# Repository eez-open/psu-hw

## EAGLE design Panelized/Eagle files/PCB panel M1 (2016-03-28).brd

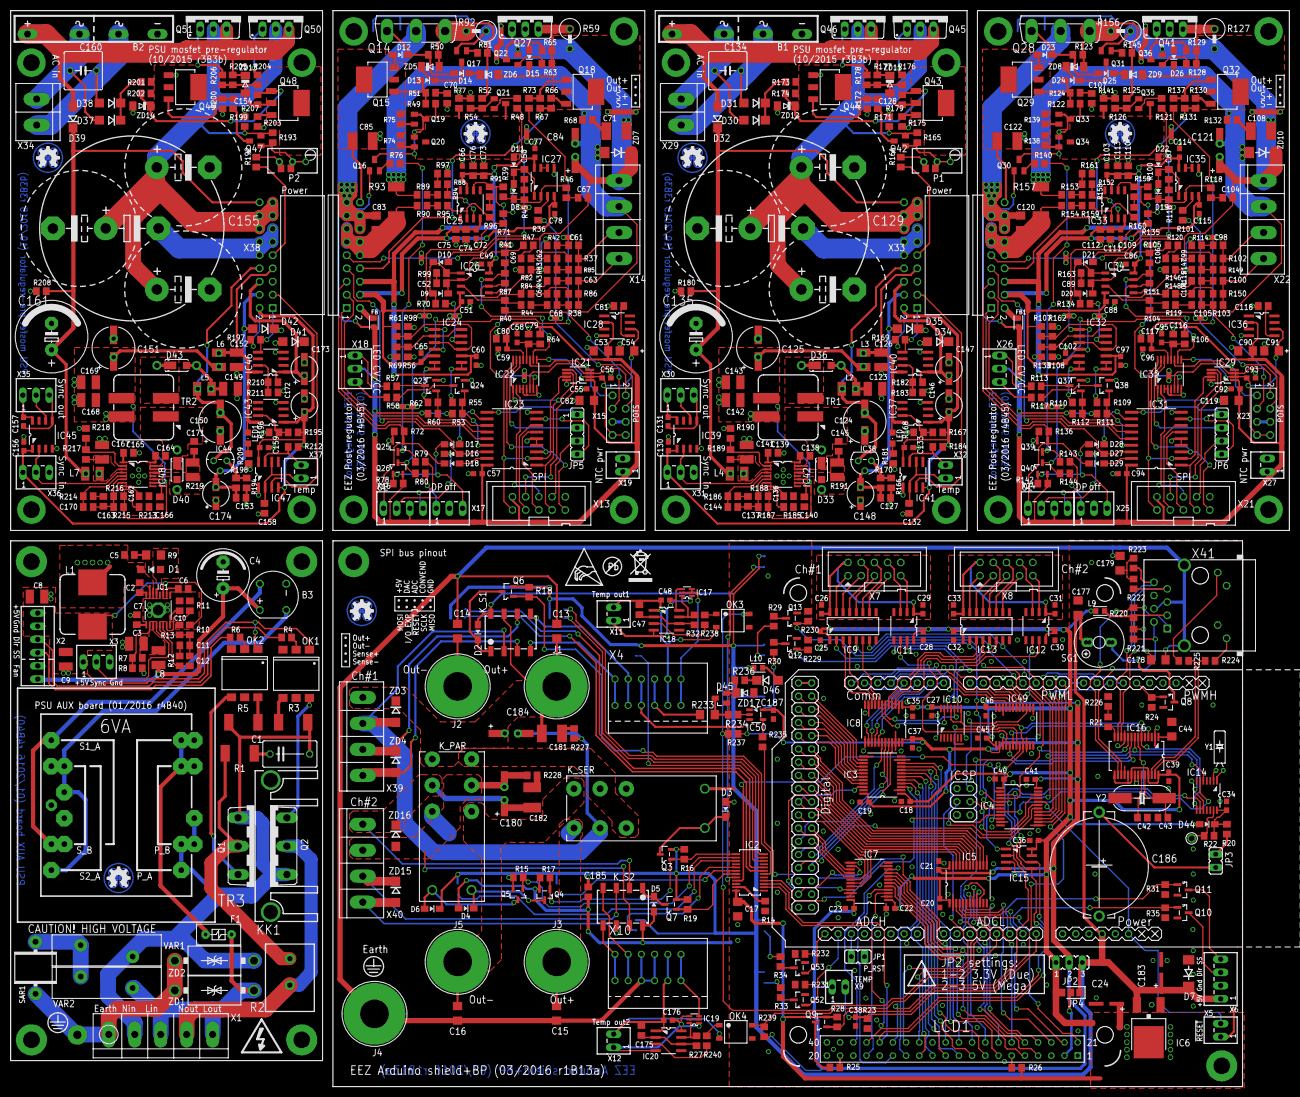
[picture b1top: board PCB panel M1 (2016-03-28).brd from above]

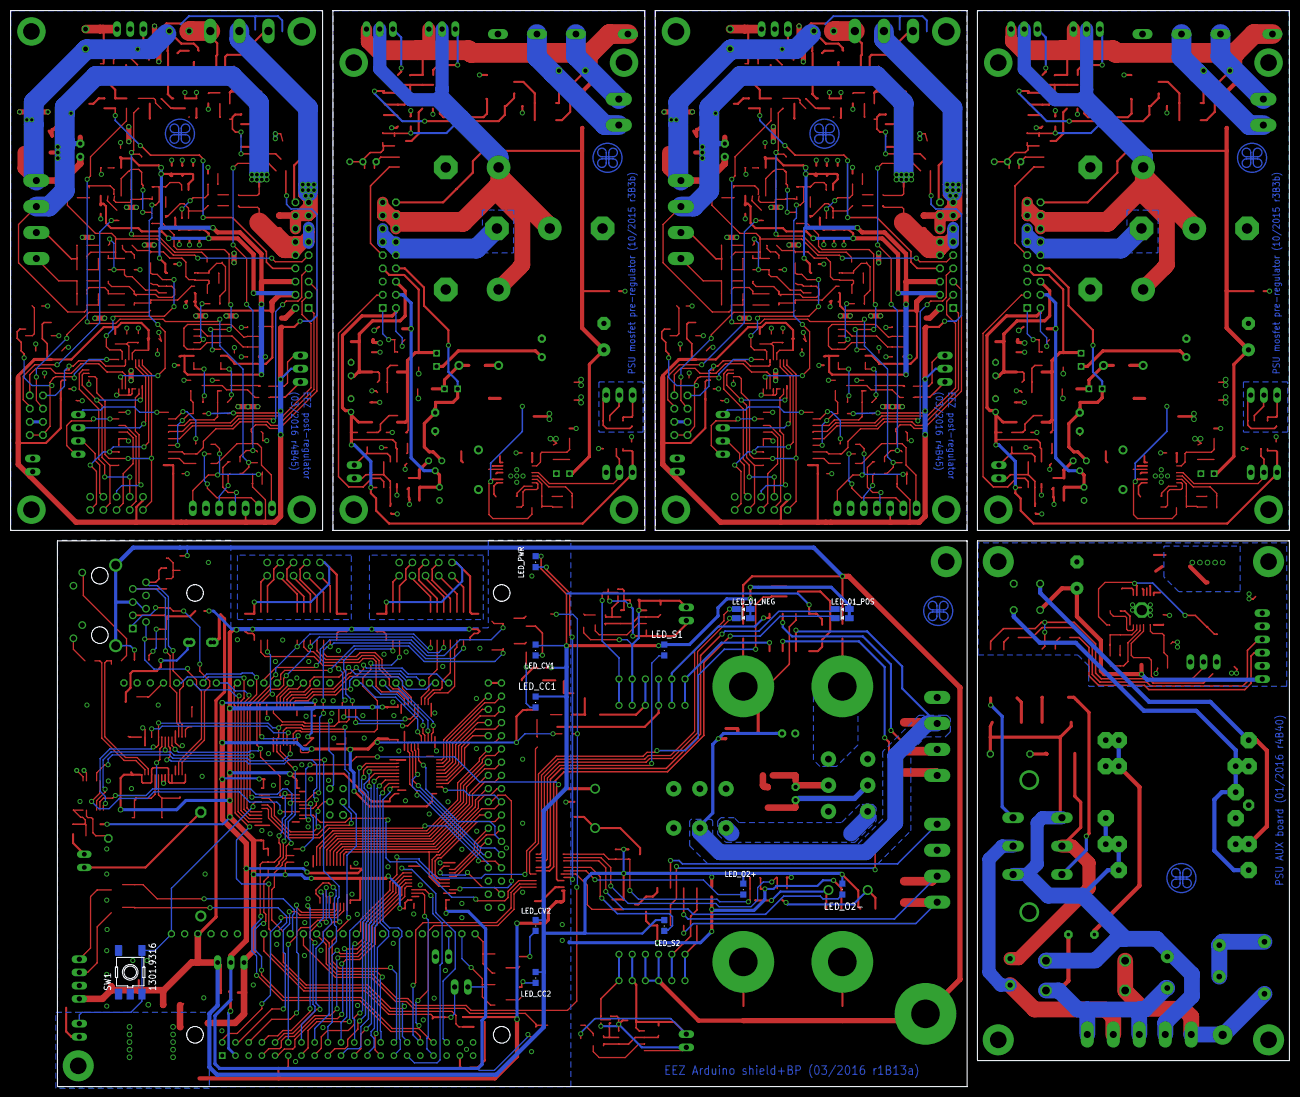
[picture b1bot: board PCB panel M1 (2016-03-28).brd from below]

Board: 3 copper layers, 246.0 x 207.0 mm, 711 parts (12 on the bottom side), 575 nets.

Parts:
B1, B2: GBI20D; GBI20
B3: B40R-DIO; RB1A
C1: 47n/400V; C075-052X106
C2, C6, C132, C138, C158, C164: 22n; C0805
C3, C8, C9: 4u7; C1210
C4: 1mF/25V; ECAP5/10.5
C5, C145, C171: 330p; C0805
C7, C127, C139, C153, C165: 100n; C0805
C10: 820p; C0805
C11: 3n9; C0805
C12: 180p; C0805
C13, C14, C15, C16, C178, C179: 10n; C1206
C17, C44, C53, C82, C90, C119, C177: 10u; C1206
C18, C19, C20, C21, C22, C23, C25, C26, C27, C28, C29, C30, C31, C32, C33, C34, C35, C36, C37, C38, C39, C40, C41, C45, C46, C48, C49, C51, C55, C56, C57, C58, C59, C60, C65, C66, C72, C77, C78, C86, C88, C92, C93, C94, C95, C96, C97, C102, C103, C109, C114, C115, C130, C131, C133, C156, C157, C159, C176, C187: 100n; C0603
C24: 10u; PANASONIC_C
C42, C43: 18p; C0805
C47, C175: 47n; C0805
C50, C67, C87, C104: 1n; C0805
C52, C89: 120p; C0805
C54, C91: 10u (Tant.); EC1206
C61, C63, C98, C100: 47p; C0805
C62, C64, C99, C101: 2n2; C0805
C68, C69, C105, C106: 1n5; C0805
C70, C74, C76, C107, C111, C113: 10n; C0805
C71, C85, C108, C122: 470n; C1812
C73, C75, C79, C80, C81, C110, C112, C116, C117, C118, C185: 1u; C0805
C83, C120: 1u/100V; C1206
C84, C121, C180, C184: 22u/63V; CAPAE660X610N_COMBO2
C123, C126, C142, C143, C149, C152, C168, C169: 2u2; C1210
C124, C125, C150, C151: 47u; CAPAE660X610N_COMBO
C128, C154: 560p; C0805
C129, C155: 10000u; ED35D+3XED22.5_COMBO
C134, C160: 1u; C050-075X075
C135, C161: 470u; ECAP5/13
C136, C162: 4n7; C0805
C137, C163: 6n8; C0805
C140, C166: 33n; C0805
C141, C167: 2u2/100V; C1210
C144, C170: n.c.; C0805
C146, C147, C172, C173: EEEFK1V100R; CAPAE430X610N_COMBO
C148, C174: EEEFK1V220R; CAPAE430X610N_COMBO
C181, C182: 470n/100V; C1812
C183: 47u; PANASONIC_C
C186: EECS5R5H105; SG-R20MM
D1: DFLS1100-7; SOD123
D2, D3, D4, D5, D6, D8, D9, D10, D11, D12, D13, D14, D15, D16, D17, D18, D19, D20, D21, D22, D23, D24, D25, D26, D27, D28, D29, D44: BAS316; SOD323-W
D7: SMBJ5.0A-TR; DO214AA
D30, D31, D32, D37, D38, D39: S1G; DO214AC
D33, D36, D40, D43: SR1100; DO34+SOD123
D34, D35, D41, D42, D46: SKL16; DO214AC
D45: BAT54S; SOT23
EEZ_SIGNATURE, EEZ_SIGNATURE1, EEZ_SIGNATURE2, EEZ_SIGNATURE3, EEZ_SIGNATURE4, EEZ_SIGNATURE5: SIGNATURESMALL; SIGNATURE_5MM
F1: LX008-V2 (80mA); POLYSWITCH-R7
FB, FB1: 60R@100MHz; BEAD0603
IC1: LM25575; SOP65P640X110-17N_HOLE
IC2: TLC5925; SOP63P600X175-24N
IC3, IC4, IC5, IC7, IC8, IC49: SN74LVCC3245ADBRSSOP; SOP65P780X200-24N
IC6: LD1117ADT33TR; DPACK
IC9, IC13: Si8660EC-B-IS1; SOIC-16
IC10: SN74LV125APW; SOP65P640X120-14N
IC11, IC12: SI8620EC-B-IS; SOIC127P600X173-8N
IC14: PCA21125; SOP65P640X120-14N
IC15: AT25256B; SOIC127P600X175-8N
IC16: ENC28J60-I/SS; SOP65P780X200-28N
IC17, IC19: BC857BS; SOT65P210X110-6N
IC18, IC20: NE555D; SOIC127P600X175-8N
IC21, IC29: DAC8552; DGK8-M
IC22, IC30: ADS1120; PW(R-PDSO-G16)
IC23, IC31: MCP23S08-E/SO; SOIC127P1030X265-18N
IC24, IC32: LP339D; SO14
IC25, IC33: OP27GSZ; SOIC127P600X173-8N
IC26, IC27, IC34, IC35: TL072D; SOIC127P600X173-8N
IC28, IC36: REF5025; SOIC127P600X175-8N
IC37, IC40, IC43, IC46: LP2951SO8; SOIC127P600X175-8N
IC38, IC44: LM337LZ; TO92
IC39, IC45: Si8610BC-B-IS; SOIC127P600X173-8N
IC41, IC47: TLC555; SOIC127P600X175-8N
IC42, IC48: LM5574; SOP65P640X110-16N
IC50: SN74LV1T34; SOT95P280X145-5N
J1, J3: BS-244DSM-R; BP_5_12
J2, J5: BS-244DSM-B; BP_5_12
J4: BS-244DSM-G; BP_5_12
JP1, JP3: 826926-2; JP1
JP2: 826926-3; JUMPER_3-PIN
JP4: 0R-JUMPA; A0R-JMP
JP5, JP6: JP4
KK1: SK145/37,5; SK145
K_PAR: RT424005; RT-C/016A5_ROUND
K_S1, K_S2: G6K-2F-5DC; G6K-2F
K_SER: RT424005; RT-C/016A5_ROUND
L1: 100uH (MSS1260-104K); MSS1278
L2, L3, L4, L5, L6, L7: 2u2; L1210_COMBO
L8: 2u2; L1210
L9, L10: 60R@100MHz; BEAD0603
LCD1: TFT_320QVT; LCD_TFT_320QVT_MIRROR
LED, LED1: HSMY-C170; CHIPLED_0805
LED_01_NEG, LED_01_POS: HSMF-C155; LED_KPB-3025
LED_CC1, LED_CC2: HSMH-C170; CHIPLED_0805
LED_CV1, LED_CV2: L-934YD; CHIPLED_0805
LED_O2+, LED_O2-: HSMG-C170; CHIPLED_0805
LED_PWR: HSMR-C170; CHIPLED_0805
LED_S1, LED_S2: HSMY-C170; CHIPLED_0805
MCU: ARDUINO+ICSP_MIRROR
OK1: MOC3052; DIL6-SMD
OK2: MOC3062; DIL6-SMD
OK3, OK4: HCPL-181
P1, P2: 500K; R_TRIM+R0805
Q1, Q2: BTA26-600; TOP3S-1
Q3, Q5, Q6, Q7, Q9: IRLML2246TRPBF; SOT95P237X112-3N
Q4, Q8, Q10, Q11, Q12, Q13, Q23, Q24, Q25, Q37, Q38, Q39, Q52, Q53: 2N7002; SOT103P240X110-3N
Q14, Q28: IRFP250N; TO247BV
Q15, Q18, Q29, Q32, Q43, Q48: BCP56-16.115; SOT230P700X180-4N
Q16, Q21, Q30, Q35: MMBT5551; SOT23-BEC
Q17, Q31: BC846C; SOT23-BEC
Q19, Q20, Q33, Q34, Q42, Q47: MMBT5401; SOT23-BEC
Q22, Q36: BC857C; SOT23-BEC
Q26, Q40: BSS84P; SOT95P237X112-3N
Q27, Q41: IRF9640; TO220B-VMOS
Q44, Q49: MCR08MT1G; SOT230P700X180-4N
Q45, Q46, Q50, Q51: IRF5210PBF; TO220B-VMOS
R1: 150R/2W; R2512
R2: 15R/7W; R_0913
R3, R5: 330R/2W; R2512
R4, R6: 270R; R0805
R7: 15K; R0805
R8, R36, R39, R50, R56, R63, R65, R100, R101, R108, R123, R128, R129: 2K2; R0805
R9: 10R; R1206
R10: 5K6 1%; R0805
R11, R185, R213: 30K; R0805
R12, R85, R86, R149, R150, R186, R214: 20K; R0805
R13: 1K8 1%; R0805
R14, R27, R32, R177, R190, R205, R218, R237, R239: 1K5; R0805
R15, R17, R24, R28, R31, R35, R72, R78, R136, R142, R229, R230, R231, R232: 100K; R0805
R16, R18, R19, R23, R171, R172, R199, R200: 4K7; R0805
R20, R54, R126, R181, R209: 560R; R0805
R21: 2K2 1%; R0805
R22, R26, R40, R41, R42, R43, R46, R70, R71, R73, R98, R104, R105, R114, R115, R118, R134, R135, R137, R162, R169, R174, R197, R202: 10K; R0805
R25, R64, R106: 10R; R0805
R29, R30, R33, R34, R57, R58, R79, R80, R113, R117, R143, R144: 240R; R0805
R37, R38, R102, R103: 2K; R0805
R44, R47, R66, R74, R75, R119, R120, R130, R138, R139: 220R; R0805
R45, R116: 11K; R0805
R48, R51, R121, R124: 470R; R0805
R49, R122, R175, R176, R178, R203, R204, R206, R236: 100R; R0805
R52, R125: 16K; R0805
R53, R60, R111, R112: 5K1; R0805
R55, R62, R109, R110: 5K6; R0805
R59, R127: 2R2/2W; 0411V
R61, R107: 12K; R0805
R67, R81, R131, R145, R234, R235: 1K; R0805
R68, R132, R227, R228: 1R; R0805
R69, R133: 47K; R0805
R76, R140: 1K8; R0805
R77, R141: 51K; R0805
R82, R87, R146, R151: 7K5; R0805
R83, R84, R147, R148: 130K; R0805
R88, R91, R152, R155, R184, R212: 3K9; R0805
R89, R90, R94, R95, R153, R154, R158, R159: 51R; R0805
R92, R156: 0R1/3W; 0411V
R93, R157: R020/2W; R2512
R96, R97, R160, R161, R238, R240: 180R; R0805
R99, R163: 0R; R0805
R164, R192: 82K; R0805
R165, R189, R193, R217: 39K; R0805
R166, R194: 604R 1%; R0805
R167, R182, R195, R210: 12K 1%; R0805
R168, R183, R196, R211: 3K9 1%; R0805
R170, R198: 200R 1%; R0805
R173, R201: 3K3; R0805
R179, R180, R207, R208: 18K; R0805
R187, R215: 30K 1%; R0805
R188, R216: 4K7 1%; R0805
R191, R219: 10R; R1210
R220, R221, R222, R223: 49R9; R0805
R224, R225: 200R; R0805
R226: 120R 1%; R0805
R233: 10K; R1206
SAR1: CG2-470L; SAR
SG1: LD-BZEN-0903; BUZZER
SH1, SH2: GND; SHORT
SH3, SH4: SHORT_2
SW1: 1301.9316; TACTM-6XN
TP1: PCB_SHIELD_TAB
TR1, TR2: MSD1260-824; MSD1260
TR3: 12V/6VA; PCB_TRAFO6VA_DUAL
U$2: RECYCLE_BIN1/8
U$3: PB_SMALL
U$4: ESD_SYMBOL
VAR1, VAR2: S20K275; VARISTOR
X1: AC_IN; TBLOCK5.0_5
X2: 22-23-2041; 22-23-2061
X3, X17, X18, X25, X26, X30, X31, X35, X36: 22-23-2031
X4, X10: MC000005; MC000005_MIRROR
X5, X9, X11, X12, X19, X27, X32, X37: 22-23-2021
X6, X16, X24: 22-23-2041
X7, X8: 09185106324; IDC-10PIN
X13, X21: 09185106324; PAK100/2500-10
X14, X22, X39, X40: 282836-4; TBLOCK5.0_4
X15, X23: TSW-104-08-L-D; TSW-104-02-S-D
X20, X28: TSW-109-08-L-D-RA
X29, X34: AC In; TBLOCK5.0_2
X33, X38: SSW-109-02-T-D-RA
X41: LMJTAB881243M-L; RJ45-TRAFO-LED
Y1: 32,768kHz; R26_XTAL
Y2: 25MHz; HC-49/4H
ZD1, ZD2: 1.5KE400CA; DO201-BIDIR
ZD3, ZD4, ZD15, ZD16: P4SMAJ60A; DO214AC
ZD5, ZD8, ZD11, ZD13: 13V; MINIMELF
ZD6, ZD9: 6V2; MINIMELF
ZD7, ZD10: P6SMB68A; DO214AA
ZD12, ZD14: 5V6; MINIMELF
ZD17: 4V3; MINIMELF

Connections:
3V3BP_SELECT: IC2.4, IC4.9
3V3LCDSD_CS: IC7.10, LCD1.38
3V3LCD_CS: IC7.4, LCD1.15
3V3LCD_DB0: IC5.3, LCD1.21
3V3LCD_DB1: IC5.4, LCD1.22
3V3LCD_DB2: IC5.5, LCD1.23
3V3LCD_DB3: IC5.6, LCD1.24
3V3LCD_DB4: IC5.7, LCD1.25
3V3LCD_DB5: IC5.8, LCD1.26
3V3LCD_DB6: IC5.9, LCD1.27
3V3LCD_DB7: IC5.10, LCD1.28
3V3LCD_DB8: IC3.10, LCD1.7
3V3LCD_DB9: IC3.9, LCD1.8
3V3LCD_DB10: IC3.8, LCD1.9
3V3LCD_DB11: IC3.7, LCD1.10
3V3LCD_DB12: IC3.6, LCD1.11
3V3LCD_DB13: IC3.5, LCD1.12
3V3LCD_DB14: IC3.4, LCD1.13
3V3LCD_DB15: IC3.3, LCD1.14
3V3LCD_RD: LCD1.6, R26.1
3V3LCD_RESET: IC7.3, LCD1.17
3V3LCD_RS: IC7.6, LCD1.4
3V3LCD_WR: IC7.5, LCD1.5
3V3MISO: IC10.8, IC10.11, IC14.8, IC15.2, IC16.6, IC49.9, LCD1.35
3V3MOSI: IC2.2, IC4.5, IC9.2, IC13.2, IC14.9, IC15.5, IC16.7, LCD1.37
3V3RTC_SELECT: IC4.8, IC14.6
3V3SCLK: IC2.3, IC4.3, IC9.7, IC13.7, IC14.10, IC15.6, IC16.8, LCD1.36
3V3TOUCH_CS: IC7.8, LCD1.30
3V3TOUCH_DIN: IC7.9, LCD1.31
3V3TOUCH_DO: IC49.8, LCD1.33
3V3TOUCH_IRQ: IC49.7, LCD1.34
3V3TOUCH_SCLK: IC7.7, LCD1.29
!3V3ADC1_SELECT: IC8.8, IC9.6
!3V3ADC2_SELECT: IC8.3, IC13.6
!3V3BP_OE: IC2.21, IC4.10
!3V3CONVEND1: IC11.6, IC49.4
!3V3CONVEND2: IC12.6, IC49.3
!3V3DAC1_SELECT: IC8.9, IC9.4
!3V3DAC2_SELECT: IC8.4, IC13.4
!3V3EEPROM_SELECT: IC4.6, IC15.1
!3V3ETH_IRQ: IC16.4, IC49.6
!3V3ETH_SELECT: IC4.7, IC16.9
!3V3IO_EXPANDER1: IC8.10, IC9.3
!3V3IO_EXPANDER2: IC8.5, IC13.3
!3V3ISOLATOR1_EN: IC8.7, IC10.13
!3V3ISOLATOR2_EN: IC8.6, IC10.10
!3V3RESET: IC4.4, IC9.5, IC13.5, IC16.10
!3V3RTC_IRQ: IC14.5, IC49.5
!ADC1_SELECT: IC8.16, MCU.15
!ADC2_SELECT: IC8.21, MCU.48
!BP_OUT1: IC2.6, Q6.1, R18.1
!BP_OUT2: IC2.7, LED_01_POS.4
!BP_OUT3: IC2.8, LED_01_POS.2
!BP_OUT5: IC2.10, LED_S1.C
!BP_OUT6: IC2.11, LED_01_NEG.4
!BP_OUT7: IC2.12, LED_01_NEG.2
!BP_OUT8: IC2.13, Q3.1, Q4.1, R16.1, R17.2
!BP_OUT9: IC2.14, Q5.1, R15.1
!BP_OUT10: IC2.15, LED_O2-.C
!BP_OUT12: IC2.17, LED_S2.C
!BP_OUT13: IC2.18, LED_O2+.C
!BP_OUT14: IC2.19, Q7.1, R19.1
!BP_OUT15: IC2.20, LED_PWR.C
!CC_ACTIVE: IC23.12, Q23.1, R60.1, R62.2
!CC_ACTIVE1: IC31.12, Q37.1, R110.2, R112.1
!CH1_ADC: IC9.11, X7.6
!CH1_DAC: IC9.13, X7.4
!CH1_EXPANDER: IC9.14, X7.3
!CH1_INT: IC11.3, X7.8
!CH1_RESET: IC9.12, X7.5
!CH2_ADC: IC13.11, X8.6
!CH2_DAC: IC13.13, X8.4
!CH2_EXPANDER: IC13.14, X8.3
!CH2_INT: IC12.3, X8.8
!CH2_RESET: IC13.12, X8.5
!CONVEND1: IC49.20, MCU.21
!CONVEND2: IC49.21, MCU.20
!CV_ACTIVE: IC23.15, Q24.1, R53.1, R55.2
!CV_ACTIVE1: IC31.15, Q38.1, R109.2, R111.1
!DAC1_SELECT: IC8.15, MCU.16
!DAC2_SELECT: IC8.20, MCU.47
!DP_DRIVE: Q18.1, R67.1, R73.1
!DP_DRIVE1: Q32.1, R131.1, R137.1
!EEPROM_SELECT: IC4.18, MCU.49
!ETH_IRQ: IC49.18, MCU.18
!ETH_SELECT: IC4.17, MCU.11
!INT: JP5.3, X13.8
!INT1: JP6.3, X21.8
!IO_EXPANDER1: IC8.14, MCU.17
!IO_EXPANDER2: IC8.19, MCU.46
!ISOLATOR1_EN: IC8.17, MCU.14
!ISOLATOR2_EN: IC8.18, MCU.45
!PS_DRDY: IC22.14, JP5.2
!PS_DRDY1: IC30.14, JP6.2
!PS_RESET: IC23.6, X13.5
!PS_RESET1: IC31.6, X21.5
!PWD_RST: JP1.1, MCU.A13
!RESET: IC4.20, MCU.RESET, SW1.3, SW1.4, X5.2
!RTC_IRQ: IC49.19, MCU.19
!SET_100%: IC23.14, X20.7
!SET_100%1: IC31.14, X28.7
!SET_DP: D17.C, IC23.11
!SET_DP1: D28.C, IC31.11
+3V3: C17.1, C18.1, C20.1, C22.1, C24.1, C25.1, C27.2, C28.1, C30.1, C32.1, C35.1, C36.1, C39.1, C40.1, C45.1, D44.A, IC2.24, IC3.1, IC4.1, IC5.1, IC6.4, IC7.1, IC8.1, IC9.1, IC10.14, IC11.8, IC12.8, IC13.1, IC15.3, IC15.7, IC15.8, IC16.15, IC16.19, IC16.20, IC16.25, IC16.28, IC49.1, JP2.1, JP4.3, L9.P$2, Q9.2, R26.2, R28.2
+5V: C177.2, C183.1, C185.1, D6.C, D7.C, IC6.3, JP2.3, JP4.1, L10.P$1, LED_01_NEG.1, LED_01_NEG.3, LED_01_POS.1, LED_01_POS.3, LED_CC1.A, LED_CC2.A, LED_CV1.A, LED_CV2.A, LED_O2+.A, LED_O2-.A, LED_PWR.A, LED_S1.A, LED_S2.A, MCU.5V, Q3.2, Q5.2, Q6.2, Q7.2, R15.2, R16.2, R18.2, R19.2, SG1.+, SG1.+B, X6.1
+5V1: C53.1, C55.2, C57.1, C59.2, C80.2, C82.1, FB.P$2, IC21.1, IC22.13, IC23.18, IC28.2, Q16.B, Q26.2, R53.2, R60.2, R64.1, R78.1, X13.2, X16.3, X18.2, X19.1
+5V2: C90.1, C92.2, C94.1, C96.2, C117.2, C119.1, FB1.P$2, IC29.1, IC30.13, IC31.18, IC36.2, Q30.B, Q40.2, R106.1, R111.2, R112.2, R142.1, X21.2, X24.3, X26.2, X27.1
+5V3: C130.1, C133.1, C146.1, C146.1.1, IC37.1, IC39.1, IC41.4, IC41.8, R167.1, R169.2, R184.2, X31.1, X33.2
+5V4: C156.1, C159.1, C172.1, C172.1.1, IC43.1, IC45.1, IC47.4, IC47.8, R195.1, R197.2, R212.2, X36.1, X38.2
+5V_CH1: C48.1, IC17.1, IC17.4, IC18.4, IC18.8, X11.1
+5V_CH2: C176.1, IC19.1, IC19.4, IC20.4, IC20.8, X12.1
+VNR: C126.1, IC37.8, IC40.8, L3.2, L3.2.1, LED.A, X33.7
+VNR1: C152.1, IC43.8, IC46.8, L6.2, L6.2.1, LED1.A, X38.7
+VREF: C54.+, C56.2, IC21.2, IC22.9, IC28.6, X15.7, X15.8
+VREF1: C91.+, C93.2, IC29.2, IC30.9, IC36.6, X23.7, X23.8
-9V: R66.2, R67.2, X20.8
-9V1: R130.2, R131.2, X28.8
-VNR: C124.2, C124.2.1, IC38.3, L2.2, L2.2.1, X33.8
-VNR1: C150.2, C150.2.1, IC44.3, L5.2, L5.2.1, X38.8
AC_EARTH: SAR1.P$2, X1.1, ZD1.C, ZD2.C
AC_IN1: C1.2, Q1.A1, Q2.A1, R3.2, R5.2, TR3.NC1, TR3.P1, TR3.P1.1, TR3.P1.2, VAR1.P$2, X1.2, ZD2.A
AC_IN2: F1.P$1, VAR2.P$1, X1.3, X1.5, ZD1.A
BATT_NTC1: MCU.A4, OK3.4, R237.2
BATT_NTC2: MCU.A3, OK4.4, R239.2
BP_OE: IC4.14, MCU.10
BP_SELECT: IC4.15, MCU.9
BUZZER: MCU.12, Q8.1, R24.2
CC_LED: R57.2, X18.1
CC_LED1: R113.2, X26.1
CH1_5VDC: C26.1, C29.1, IC9.16, IC11.1, X7.2
CH1_GND: C26.2, C29.2, IC9.9, IC11.4, X7.10
CH1_MISO: IC11.2, X7.9
CH1_MOSI: IC9.15, X7.1
CH1_SCLK: IC9.10, X7.7
CH2_5VDC: C31.1, C33.1, IC12.1, IC13.16, X8.2
CH2_GND: C31.2, C33.2, IC12.4, IC13.9, X8.10
CH2_MISO: IC12.2, X8.9
CH2_MOSI: IC13.15, X8.1
CH2_SCLK: IC13.10, X8.7
CS_ADC: IC22.2, X13.6
CS_ADC1: IC30.2, X21.6
CS_DAC: IC21.5, X13.4
CS_DAC1: IC29.5, X21.4
CS_EXPANDER: IC23.7, X13.3
CS_EXPANDER1: IC31.7, X21.3
CV_LED: R58.1, X18.3
CV_LED1: R117.1, X26.3
DC_IN: C83.1, Q14.D, X20.14, X20.15, X20.16, X20.17
DC_IN1: C120.1, Q28.D, X28.14, X28.15, X28.16, X28.17
DC_IN2: B1.+, D32.A, Q45.S, Q46.S, R177.1, ZD11.C
DC_IN3: B2.+, D39.A, Q50.S, Q51.S, R205.1, ZD13.C
DC_OUT: C135.+, D32.C, L4.1, L4.1.1, R180.1, X33.18
DC_OUT1: C161.+, D39.C, L7.1, L7.1.1, R208.1, X38.18
DC_PREG1: C141.1, IC42.3, L4.2, L4.2.1, R189.2
DC_PREG2: C167.1, IC48.3, L7.2, L7.2.1, R217.2
DC_PREG3: C3.1, IC1.3, L8.2, R7.2
DP_LED: Q26.3, R73.2, R80.2
DP_LED1: Q40.3, R137.2, R144.2
EARTH: C13.2, C14.1, C15.2, C16.1, C178.2, C179.2, J4.P$1, X10.3, X10.3.1, X10.4, X10.4.1, X41.4, X41.5, X41.SH1, X41.SH2
ETH_IN+: IC16.13, R223.1, X41.8
ETH_IN-: IC16.12, R222.2, X41.7
ETH_LEDA: IC16.26, R225.1
ETH_LEDB: IC16.27, R224.1
ETH_OUT+: IC16.17, R221.1, X41.2
ETH_OUT-: IC16.16, R220.2, X41.1
EXT_TRIG: MCU.A7, R235.1
GND: B3.-, C3.2, C4.-, C6.2, C7.1, C8.2, C9.2, C10.1, IC1.9, IC1.12, IC1.TP, IC1.TP2, R8.1, R11.2, R13.2, X2.2, X2.5, X3.3
GND1: C49.1, C51.1, C53.2, C54.-, C55.1, C56.1, C57.2, C58.1, C59.1, C60.1, C65.1, C66.2, C70.2, C72.2, C73.1, C74.1, C75.1, C76.1, C77.1, C78.1, C79.1, C80.1, C81.2, C82.2, C83.2, C85.2, IC21.8, IC22.3, IC22.4, IC22.5, IC22.8, IC23.4, IC23.5, IC23.9, IC27.5, IC28.4, Q23.2, Q24.2, Q25.2, Q27.D, R54.1, R56.1, R72.1, R77.1, R82.1, R97.1, R98.2, SH1.1, X13.10, X15.5, X15.6, X17.2, X19.2, X20.12
GND2: C86.1, C88.1, C90.2, C91.-, C92.1, C93.1, C94.2, C95.1, C96.1, C97.1, C102.1, C103.2, C107.2, C109.2, C110.1, C111.1, C112.1, C113.1, C114.1, C115.1, C116.1, C117.1, C118.2, C119.2, C120.2, C122.2, IC29.8, IC30.3, IC30.4, IC30.5, IC30.8, IC31.4, IC31.5, IC31.9, IC35.5, IC36.4, Q37.2, Q38.2, Q39.2, Q41.D, R108.1, R126.1, R136.1, R141.1, R146.1, R161.1, R162.2, SH2.1, X21.10, X23.5, X23.6, X25.2, X27.2, X28.12
GND4: B1.-, C123.2, C124.1, C124.1.1, C125.2, C125.2.1, C126.2, C127.1, C129.-, C129.-1, C129.-2, C129.-3, C130.2, C132.1, C133.2, C135.-, C136.1, C139.1, C140.2, C141.2, C142.2, C143.2, C146.2, C146.2.1, C147.2, C147.2.1, C148.1, C148.1.1, D34.A, D35.C, IC37.4, IC39.4, IC40.4, IC41.1, IC42.9, IC42.12, Q44.1, R166.2, R168.2, R172.2, R175.2, R179.2, R180.2, R181.2, R183.2, R185.2, R188.2, R190.1, SH3.2, TR1.4, X31.3, ZD12.A
GND6: B2.-, C149.2, C150.1, C150.1.1, C151.2, C151.2.1, C152.2, C153.1, C155.-, C155.-1, C155.-2, C155.-3, C156.2, C158.1, C159.2, C161.-, C162.1, C165.1, C166.2, C167.2, C168.2, C169.2, C172.2, C172.2.1, C173.2, C173.2.1, C174.1, C174.1.1, D41.A, D42.C, IC43.4, IC45.4, IC46.4, IC47.1, IC48.9, IC48.12, Q49.1, R194.2, R196.2, R200.2, R203.2, R207.2, R208.2, R209.2, R211.2, R213.2, R216.2, R218.1, SH4.2, TR2.4, X36.3, ZD14.A
GND7: C17.2, C18.2, C19.1, C20.2, C21.1, C22.2, C23.1, C24.2, C25.2, C27.1, C28.2, C30.2, C32.2, C34.1, C35.2, C36.2, C37.1, C38.1, C39.2, C40.2, C41.1, C42.2, C43.2, C44.1, C45.2, C46.1, C177.1, C183.2, C185.2, C186.2, C187.2, D2.A, D3.A, D4.A, D5.A, D7.A, D45.1, IC2.1, IC3.2, IC3.11, IC3.12, IC3.13, IC4.2, IC4.11, IC4.12, IC4.13, IC4.22, IC5.2, IC5.11, IC5.12, IC5.13, IC6.1, IC7.2, IC7.11, IC7.12, IC7.13, IC7.22, IC8.2, IC8.11, IC8.12, IC8.13, IC8.22, IC9.8, IC10.1, IC10.2, IC10.4, IC10.5, IC10.7, IC11.5, IC12.5, IC13.8, IC14.7, IC15.4, IC16.2, IC16.11, IC16.18, IC16.21, IC16.22, IC49.10, IC49.11, IC49.12, IC49.13, IC49.22, IC50.3, JP1.2, K_S1.8, K_S2.8, K_SER.A1, LCD1.1, MCU.GND, MCU.GND1, MCU.GND2, MCU.GND3, MCU.GND4, MCU.ICSP_GND, OK3.3, OK4.3, Q4.2, Q8.2, Q10.2, Q11.2, Q12.2, Q13.2, Q52.2, Q53.2, R14.1, R17.1, R23.2, R24.1, R31.2, R35.2, R226.2, R229.2, R230.2, R231.2, R232.2, SW1.1, SW1.2, SW1.5, X4.4, X4.4.1, X5.1, X6.2, X41.10, X41.11, ZD17.A
GND_CH1: C47.1, C48.2, IC18.1, OK3.2, X4.2, X4.2.1, X11.2
GND_CH2: C175.1, C176.2, IC20.1, OK4.2, X10.2, X10.2.1, X12.2
INT_EXP: IC23.8, JP5.4
INT_EXP1: IC31.8, JP6.4
IS1: D33.A, D33.A.1, IC42.13, R191.1
IS2: D40.A, D40.A.1, IC48.13, R219.1
IS3: D1.A, IC1.13, R9.1
ISENSE+: IC25.3, R88.2, R94.2
ISENSE+1: IC33.3, R152.2, R158.2
ISENSE-: IC25.2, R95.2, R96.1
ISENSE-1: IC33.2, R159.2, R160.1
I_MON: IC22.7, IC25.6, R39.1, R91.2
I_MON1: IC30.7, IC33.6, R100.1, R155.2
I_SERVO: C50.2, D8.A, D11.C, IC27.1, R71.1
I_SERVO1: C87.2, D19.A, D22.C, IC35.1, R135.1
I_SET: R36.1, X15.4
I_SET1: R101.1, X23.4
I_SET_IN: IC21.3, IC22.6, X15.2
I_SET_IN1: IC29.3, IC30.6, X23.2
LCDSD_CS: IC7.14, MCU.53
LCD_BRIGHTNESS: MCU.7, Q9.1, R28.1
LCD_CS: IC3.22, IC5.22, IC7.20, MCU.39
LCD_DB0: IC5.21, MCU.37
LCD_DB1: IC5.20, MCU.36
LCD_DB2: IC5.19, MCU.35
LCD_DB3: IC5.18, MCU.34
LCD_DB4: IC5.17, MCU.33
LCD_DB5: IC5.16, MCU.32
LCD_DB6: IC5.15, MCU.31
LCD_DB7: IC5.14, MCU.30
LCD_DB8: IC3.14, MCU.22
LCD_DB9: IC3.15, MCU.23
LCD_DB10: IC3.16, MCU.24
LCD_DB11: IC3.17, MCU.25
LCD_DB12: IC3.18, MCU.26
LCD_DB13: IC3.19, MCU.27
LCD_DB14: IC3.20, MCU.28
LCD_DB15: IC3.21, MCU.29
LCD_RESET: IC7.21, MCU.38
LCD_RS: IC7.18, MCU.41
LCD_WR: IC7.19, MCU.40
LED_A: LCD1.19, R25.2
LED_CC1: MCU.4, Q12.1, R229.1
LED_CC2: MCU.A14, Q52.1, R231.1
LED_CV1: MCU.5, Q13.1, R230.1
LED_CV2: MCU.A15, Q53.1, R232.1
MISO: IC49.15, MCU.ICSP_MISO
MOSI: IC4.19, MCU.ICSP_MOSI
unnamed: IC26.3, R40.2, R44.2
unnamed: C52.1, D9.C, IC26.2, R41.2, R47.2
unnamed: C64.1, R84.2, R86.1
unnamed: C61.2, R42.1
unnamed: C11.2, R12.2
unnamed: C11.1, C12.1, IC1.6, R10.2, R13.1
unnamed: C2.2, IC1.16
unnamed: C12.2, IC1.5, R12.1
unnamed: IC1.7, R11.1
unnamed: C7.2, IC1.1
unnamed: C10.2, IC1.8
unnamed: C6.1, IC1.10
unnamed: IC1.4, X3.2
unnamed: F1.P$2, TR3.P2, TR3.P2.1, TR3.P2.2
unnamed: B3.AC2, TR3.S1.2, TR3.S1.2A, TR3.S1.2NC, TR3.S2.2
unnamed: B3.AC1, TR3.S1.1, TR3.S2.1, TR3.S2.1A
unnamed: IC1.2, R7.1, R8.2
unnamed: SAR1.P$1, VAR1.P$1, VAR2.P$2
unnamed: C5.2, R9.2
unnamed: Q2.A2, R2.2, X1.4
unnamed: C1.1, R1.1
unnamed: C63.2, R43.1
unnamed: Q1.A2, R1.2, R2.1
unnamed: OK1.6, Q2.G
unnamed: OK2.4, Q1.G
unnamed: C67.2, R46.1
unnamed: OK2.6, R5.1
unnamed: OK1.2, R4.1
unnamed: OK2.2, R6.1
unnamed: OK1.4, R3.1
unnamed: D2.C, K_S1.1, Q6.3
unnamed: D8.C, IC27.2, R39.2, R45.2, R46.2
unnamed: C68.2, R44.1
unnamed: D5.C, K_S2.1, Q7.3
unnamed: C69.2, R47.1
unnamed: Q23.3, R57.1
unnamed: Q18.3, R66.1
unnamed: Q22.B, R63.2
unnamed: C58.2, C79.2, IC22.12, R64.2
unnamed: D17.A, Q26.1, R78.2, X17.3
unnamed: Q21.B, R52.1, R54.2
unnamed: IC24.1, IC24.2, R55.1
unnamed: D16.C, X16.2
unnamed: R80.1, X17.1
unnamed: IC24.13, IC24.14, R62.1
unnamed: R79.1, X16.4
unnamed: IC27.3, R36.2
unnamed: C81.1, IC28.5
unnamed: FB.P$1, X20.2
unnamed: Q24.3, R58.2
unnamed: D10.A, D11.A, R48.1
unnamed: R89.2, R94.1
unnamed: D12.C, D14.A, Q14.G, R50.1
unnamed: R90.2, R95.1
unnamed: R91.1, R96.2
unnamed: R88.1, R97.2
unnamed: IC27.6, IC27.7
unnamed: C52.2, R99.1
unnamed: D12.A, Q15.3
unnamed: IC23.10, JP5.1
unnamed: IC35.3, R101.2
unnamed: D13.A, Q15.1, R49.1, R51.2
unnamed: IC34.3, R104.2, R119.2
unnamed: C70.1, R51.1
unnamed: C89.1, D20.C, IC34.2, R105.2, R120.2
unnamed: IC31.10, JP6.1
unnamed: C95.2, C116.2, IC30.12, R106.2
unnamed: LED_CV1.C, R29.2
unnamed: IC32.1, IC32.2, R109.1
unnamed: IC34.5, R114.2, R146.2, R147.1
unnamed: IC34.6, R115.2, R148.1, R151.2
unnamed: C101.1, R148.2, R150.1
unnamed: C99.1, R147.2, R149.1
unnamed: C98.2, R114.1
unnamed: C100.2, R115.1
unnamed: C104.2, R118.1
unnamed: D19.C, IC35.2, R100.2, R116.2, R118.2
unnamed: C105.2, R119.1
unnamed: LED_CV2.C, R34.2
unnamed: LED_CC2.C, R33.1
unnamed: C106.2, R120.1
unnamed: D21.A, D22.A, R121.1
unnamed: D23.C, D25.A, Q28.G, R123.1
unnamed: D23.A, Q29.3
unnamed: D24.A, Q29.1, R122.1, R124.2
unnamed: D24.C, Q31.C, ZD8.C
unnamed: C107.1, R124.1
unnamed: D25.C, ZD9.C
unnamed: Q41.S, R127.1, R128.1, R129.1
unnamed: D26.A, Q36.C, Q41.G, R129.2
unnamed: Q35.E, R121.2
unnamed: C108.2, R132.2
unnamed: C42.1, IC16.23, Y2.2
unnamed: C43.1, IC16.24, Y2.1
unnamed: C44.2, IC16.1
unnamed: IC32.13, IC32.14, R110.1
unnamed: IC16.14, R21.1
unnamed: IC32.5, IC32.6, R134.2
unnamed: IC32.8, IC32.11, R135.2
unnamed: IC32.7, IC32.9, R108.2, R133.1
unnamed: IC32.4, IC32.10, R107.2, R162.1
unnamed: Q34.E, R138.1
unnamed: Q33.E, R139.1
unnamed: Q30.E, R140.2
unnamed: C34.2, D44.C, IC14.14, R20.2, R22.1
unnamed: Q35.B, R125.1, R126.2
unnamed: Q37.3, R113.1
unnamed: Q31.B, R145.1
unnamed: C87.1, R116.1
unnamed: Q32.3, R130.1
unnamed: IC14.13, R22.2, TP1.1
unnamed: C186.1, JP3.2
unnamed: C62.1, R83.2, R85.1
unnamed: Q36.B, R128.2
unnamed: D28.A, Q40.1, R142.2, X25.3
unnamed: D27.C, X24.2
unnamed: R144.1, X25.1
unnamed: R143.1, X24.4
unnamed: C118.1, IC36.5
unnamed: Q8.3, SG1.-, SG1.-B
unnamed: C47.2, IC18.2, IC18.6, R32.2
unnamed: FB1.P$1, X28.2
unnamed: Q38.3, R117.2
unnamed: R153.2, R158.1
unnamed: D13.C, Q17.C, ZD5.C
unnamed: R154.2, R159.1
unnamed: R155.1, R160.2
unnamed: R152.1, R161.2
unnamed: IC35.6, IC35.7
unnamed: C89.2, R163.1
unnamed: B1.AC1, C134.1, D30.A, X29.2
unnamed: B1.AC2, C134.2, D31.A, X29.1
unnamed: P1.1, P1.A, P1.S, Q42.B, R165.1
unnamed: IC37.7, R167.2, R168.1
unnamed: Q43.3, R175.1
unnamed: D30.C, D31.C, R173.1
unnamed: Q44.3, R171.2, R172.1
unnamed: C128.2, Q43.1, R174.2, ZD12.C
unnamed: D14.C, ZD6.C
unnamed: Q46.G, R178.1
unnamed: Q21.E, R48.2
unnamed: Q27.S, R59.1, R63.1, R65.1
unnamed: D15.A, Q22.C, Q27.G, R65.2
unnamed: Q42.C, R171.1
unnamed: C71.2, R68.2
unnamed: IC26.5, R42.2, R82.2, R83.1
unnamed: IC10.12, IC11.7
unnamed: Q45.G, R176.1
unnamed: IC24.5, IC24.6, R70.2
unnamed: SH3.1, X33.10, X33.11, X33.12, X33.13
unnamed: D3.C, K_SER.A2, Q3.3
unnamed: D6.A, K_PAR.A2, Q5.3
unnamed: IC39.6, X30.2
unnamed: IC26.6, R43.2, R84.1, R87.2
unnamed: IC40.7, R182.2, R183.1
unnamed: LED.C, R181.1
unnamed: IC24.8, IC24.11, R71.2
unnamed: C137.2, R186.2
unnamed: C137.1, C144.1, IC42.6, R187.2, R188.1
unnamed: IC10.9, IC12.7
unnamed: C138.2, IC42.16
unnamed: C144.2, IC42.5, R186.1
unnamed: IC42.7, R185.1
unnamed: C139.2, IC42.1
unnamed: C136.2, IC42.8
unnamed: IC24.7, IC24.9, R56.2, R69.1
unnamed: C140.1, IC42.10
unnamed: C50.1, R45.1
unnamed: C145.2, R191.2
unnamed: P1.2, P1.E, R164.1
unnamed: B2.AC1, C160.1, D37.A, X34.2
unnamed: B2.AC2, C160.2, D38.A, X34.1
unnamed: IC24.4, IC24.10, R61.2, R98.1
unnamed: C149.1, D43.A, D43.A.1, L5.1, L5.1.1
unnamed: C123.1, D36.A, D36.A.1, L2.1, L2.1.1
unnamed: IC42.2, R189.1, R190.2
unnamed: P2.1, P2.A, P2.S, Q47.B, R193.1
unnamed: IC43.7, R195.2, R196.1
unnamed: Q20.E, R74.1
unnamed: Q19.E, R75.1
unnamed: R192.2, X38.9
unnamed: Q16.E, R76.2
unnamed: R164.2, X33.9
unnamed: IC41.7, R184.1, X32.2
unnamed: IC44.1, R194.1, R198.2
unnamed: C132.2, IC41.2, IC41.6, X32.1
unnamed: Q48.3, R203.1
unnamed: D37.C, D38.C, R201.1
unnamed: C131.1, IC39.8, X30.1
unnamed: Q49.3, R199.2, R200.1
unnamed: C154.2, Q48.1, R202.2, ZD14.C
unnamed: Q51.G, R206.1
unnamed: Q47.C, R199.1
unnamed: C131.2, IC39.5, X30.3
unnamed: Q50.G, R204.1
unnamed: SH4.1, X38.10, X38.11, X38.12, X38.13
unnamed: Q17.B, R81.1
unnamed: IC38.1, R166.1, R170.2
unnamed: C157.1, IC45.8, X35.1
unnamed: C157.2, IC45.5, X35.3
unnamed: IC45.6, X35.2
unnamed: IC46.7, R210.2, R211.1
unnamed: IC47.7, R212.1, X37.2
unnamed: C158.2, IC47.2, IC47.6, X37.1
unnamed: LED1.C, R209.1
unnamed: C163.2, R214.2
unnamed: C163.1, C170.1, IC48.6, R215.2, R216.1
unnamed: C164.2, IC48.16
unnamed: C170.2, IC48.5, R214.1
unnamed: IC48.7, R213.1
unnamed: C165.2, IC48.1
unnamed: C162.2, IC48.8
unnamed: C166.1, IC48.10
unnamed: IC48.2, R217.1, R218.2
unnamed: C171.2, R219.2
unnamed: P2.2, P2.E, R192.1
unnamed: C175.2, IC20.2, IC20.6, R27.2
unnamed: IC19.6, IC20.7, R27.1
unnamed: IC17.6, IC18.7, R32.1
unnamed: JP4.2, LCD1.2
unnamed: Q9.3, R25.1
unnamed: Q12.3, R30.2
unnamed: Q13.3, R29.1
unnamed: LED_CC1.C, R30.1
unnamed: Q52.3, R33.2
unnamed: Q53.3, R34.1
unnamed: MCU.5V(1), MCU.5V(2)
unnamed: IC14.1, Y1.2
unnamed: IC14.2, Y1.1
unnamed: R225.2, X41.12
unnamed: R224.2, X41.9
unnamed: C179.1, R222.1, R223.2
unnamed: C178.1, L9.P$1, R220.1, R221.2, X41.3
unnamed: R21.2, R226.1
unnamed: C181.2, R227.2
unnamed: C182.2, R228.2
unnamed: K_S1.6, X39.P$3, ZD4.C
unnamed: K_S1.3, X39.P$4, ZD4.A
unnamed: K_S2.6, X40.P$4, ZD15.A
unnamed: K_S2.3, X40.P$3, ZD15.C
unnamed: D45.3, R233.2, R234.2
unnamed: IC50.2, R234.1
unnamed: IC50.4, R235.2
unnamed: D45.2, R236.1, ZD17.C
unnamed: D46.C, R236.2
unnamed: D46.A, L10.P$2
unnamed: R233.1, X4.3, X4.3.1
unnamed: JP3.1, R20.1
unnamed: OK3.1, R238.2
unnamed: OK4.1, R240.2
unnamed: IC2.23, R14.2
NTC1: IC17.2, IC17.3, IC17.5, X4.1, X4.1.1
NTC2: IC19.2, IC19.3, IC19.5, X10.1, X10.1.1
OE_DRIVE: Q25.3, R76.1, R79.2
OE_DRIVE1: Q39.3, R140.1, R143.2
OUT1+: C13.1, C181.1, C184.1, C184.1.1, J1.P$1, K_PAR.14A, K_S1.7, X39.P$1, ZD3.C
OUT1-: C14.2, J2.P$1, K_PAR.14B, K_SER.11B, K_SER.12A
OUT2+: C15.1, J3.P$1, K_PAR.12A, K_SER.14A
OUT2-: C16.2, J5.P$1, K_PAR.12B, K_SER.14B
OUT+: C62.2, C67.1, C69.1, C71.1, C84.1, C84.1.1, Q17.E, Q22.E, R37.1, R59.2, R92.1, X14.P$1, X20.9, ZD7.C
OUT+1: C99.2, C104.1, C106.1, C108.1, C121.1, C121.1.1, Q31.E, Q36.E, R102.1, R127.2, R156.1, X22.P$1, X28.9, ZD10.C
OUT-: C64.2, C68.1, C84.2, C84.2.1, R38.2, R68.1, R89.1, R93.1, X14.P$2, ZD7.A
OUT-1: C101.2, C105.1, C121.2, C121.2.1, R103.2, R132.1, R153.1, R157.1, X22.P$2, ZD10.A
POUT: C129.+, C129.+2, C129.+3, Q42.E, Q45.D, Q46.D, R165.2, R179.1, X33.14, X33.15, X33.16, X33.17
POUT1: C155.+, C155.+2, C155.+3, Q47.E, Q50.D, Q51.D, R193.2, R207.1, X38.14, X38.15, X38.16, X38.17
POUT-: R90.1, R93.2, SH1.2, X20.10, X20.11, X20.13
POUT-1: R154.1, R157.2, SH2.2, X28.10, X28.11, X28.13
PREG_EN: D18.C, Q25.1, R72.2, X16.1, X20.5
PREG_EN1: D29.C, Q39.1, R136.2, X24.1, X28.5
PS_MISO: IC22.15, IC23.3, X13.9
PS_MISO1: IC30.15, IC31.3, X21.9
PS_MOSI: IC21.7, IC22.16, IC23.2, X13.1
PS_MOSI1: IC29.7, IC30.16, IC31.2, X21.1
PS_SCLK: IC21.6, IC22.1, IC23.1, X13.7
PS_SCLK1: IC29.6, IC30.1, IC31.1, X21.7
PWRDIR: MCU.A1, Q10.1, R35.1
PWRGOOD: D16.A, IC23.16, X20.1
PWRGOOD1: D27.A, IC31.16, X28.1
PWRGOOD2: IC40.5, R169.1, X33.1
PWRGOOD3: IC46.5, R197.1, X38.1
PWRSS: MCU.A2, Q11.1, R31.1
PWR_DIRECT: R4.2, X2.3
PWR_DIRECT2: Q10.3, X6.3
PWR_IN1-: C184.2, C184.2.1, K_S1.2, K_SER.11A, R227.1, X39.P$2, ZD3.A
PWR_IN2+: C180.1, C180.1.1, C182.1, K_PAR.11A, K_S2.2, X40.P$1, ZD16.C
PWR_IN2-: C180.2, C180.2.1, K_PAR.11B, K_S2.7, R228.1, X40.P$2, ZD16.A
PWR_SSTART: R6.2, X2.4
PWR_SSTART1: Q11.3, X6.4
Q4A: Q44.2, Q44.4, R173.2, R174.1
Q4A1: Q49.2, Q49.4, R201.2, R202.1
Q4_OUT: Q14.S, R50.2, R52.2, R81.2, R92.2, ZD5.A
Q4_OUT1: Q28.S, R123.2, R125.2, R145.2, R156.2, ZD8.A
Q5C: C128.1, Q43.2, Q43.4, R176.2, R177.2, R178.2, ZD11.A
Q5C1: C154.1, Q48.2, Q48.4, R204.2, R205.2, R206.2, ZD13.A
Q6C: D15.C, Q18.2, Q18.4, ZD6.A
Q6C1: D26.C, Q32.2, Q32.4, ZD9.A
Q7C: Q16.C, Q19.B, Q19.C, Q20.B
Q7C1: Q30.C, Q33.B, Q33.C, Q34.B
Q8C: Q20.C, Q21.C, R49.2, R77.2
Q8C1: Q34.C, Q35.C, R122.2, R141.2
RTC_SELECT: IC4.16, MCU.8
SCLK: IC4.21, MCU.ICSP_SCK
SENSE1+: K_S1.5, X4.5, X4.5.1
SENSE1-: K_S1.4, X4.6, X4.6.1
SENSE2+: K_S2.4, X10.5, X10.5.1
SENSE2-: K_S2.5, X10.6, X10.6.1
SENSE+: C61.1, R37.2, R85.2, X14.P$3
SENSE+1: C98.1, R102.2, R149.2, X22.P$3
SENSE-: C63.1, R38.1, R86.2, X14.P$4
SENSE-1: C100.1, R103.1, R150.2, X22.P$4
SET_OE: D18.A, IC23.17
SET_OE1: D29.A, IC31.17
SW1: C138.1, C145.1, D33.C, D33.C.1, IC42.14, IC42.15, TR1.1
SW2: C164.1, C171.1, D40.C, D40.C.1, IC48.14, IC48.15, TR2.1
SW3: C2.1, C5.1, D1.C, IC1.14, IC1.15, L1.1
SYNC: IC39.2, IC42.4, X31.2
SYNC1: IC45.2, IC48.4, X36.2
TEMP_ANALOG: C38.2, MCU.A0, R23.1, X9.2
TEMP_FREQ: IC23.13, X20.3
TEMP_FREQ1: IC18.3, R238.1
TEMP_FREQ2: IC20.3, R240.1
TEMP_FREQ3: IC31.13, X28.3
TEMP_FREQ4: IC41.3, X33.3
TEMP_FREQ5: IC47.3, X38.3
TOUCH_CS: IC7.16, MCU.43
TOUCH_DIN: IC7.15, MCU.42
TOUCH_DOUT: IC49.16, MCU.3
TOUCH_IRQ: IC49.17, MCU.2
TOUCH_SCLK: IC7.17, MCU.44
U_MON: IC22.10, IC26.7, R41.1, R87.1
U_MON1: IC30.10, IC34.7, R105.1, R151.1
U_SERVO: D9.A, D10.C, IC26.1, R70.1, R99.2
U_SERVO1: D20.A, D21.C, IC34.1, R134.1, R163.2
U_SET: R40.1, X15.3
U_SET1: R104.1, X23.3
U_SET_IN: IC21.4, IC22.11, X15.1
U_SET_IN1: IC29.4, IC30.11, X23.1
V+: C49.2, C60.2, C66.1, C73.2, C76.2, C77.2, IC24.3, IC25.7, IC26.8, IC27.8, R69.2, X20.6
V+1: C86.2, C97.2, C103.1, C110.2, C113.2, C114.2, IC32.3, IC33.7, IC34.8, IC35.8, R133.2, X28.6
V+2: C147.1, C147.1.1, D34.C, IC40.1, R182.1, X33.6
V+3: C173.1, C173.1.1, D41.C, IC46.1, R210.1, X38.6
V-: C51.2, C65.2, C72.1, C74.2, C75.2, C78.2, IC24.12, IC25.4, IC26.4, IC27.4, R61.1, X20.4
V-1: C88.2, C102.2, C109.1, C111.2, C112.2, C115.2, IC32.12, IC33.4, IC34.4, IC35.4, R107.1, X28.4
V-2: D4.C, K_PAR.A1, Q4.3
V-3: C127.2, C148.2, C148.2.1, D35.A, IC38.2, R170.1, X33.4
V-4: C153.2, C174.2, C174.2.1, D42.A, IC44.2, R198.1, X38.4
VBIAS: C85.1, Q15.2, Q15.4, R74.2, R75.2, X20.18
VBIAS1: C122.1, Q29.2, Q29.4, R138.2, R139.2, X28.18
VCC: C19.2, C21.2, C23.2, C37.2, C41.2, C46.2, C187.1, IC3.24, IC4.24, IC5.24, IC7.24, IC8.24, IC49.2, IC49.24, IC50.5, JP2.2, R237.1, R239.1, X9.1
VIN1: B3.+, C4.+, L8.1, X2.6
VOUT: C8.1, C9.1, IC1.11, L1.2, OK1.1, OK2.1, R10.1, X2.1, X3.1
VOUT+: C125.1, C125.1.1, C142.1, C143.1, IC42.11, L3.1, L3.1.1, R187.1, TR1.3
VOUT+1: C151.1, C151.1.1, C168.1, C169.1, IC48.11, L6.1, L6.1.1, R215.1, TR2.3
VOUT-: D36.C, D36.C.1, TR1.2
VOUT-1: D43.C, D43.C.1, TR2.2

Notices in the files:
parts and their libraries:
EEZ_Lib1: This work is licensed under a Creative Commons Attribution-ShareAlike 4.0 International License.
